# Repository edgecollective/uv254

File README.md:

# uv254

Open hardware for the **uv254** UV water-quality sensor. The device is three
boards, each its own KiCad project:

| Board | Folder | What's on it | Current design |
|---|---|---|---|
| **UV-Control** | [`hardware/uv-control`](hardware/uv-control) | nRF52840 controller (from Rook v0.4), ADS1115 ADC, color TFT, microSD, buttons | v0.4 (in progress: restarted from Rook v0.4) |
| **UV-Emitter** | [`hardware/uv-emitter`](hardware/uv-emitter) | Inolux IN-C35PPCTGU0 UV-C LED and its driver | v0.4 (released 2026-11-08) |
| **UV-Detector** | [`hardware/uv-detector`](hardware/uv-detector) | SD008-2171-112 photodiode with an op-amp front end | v0.5 (in progress: 3.3 V, 1.8 V reference, 7-pin connector); v0.4 released 2026-11-08 |

| [UV-Control](hardware/uv-control) | [UV-Emitter](hardware/uv-emitter) | [UV-Detector](hardware/uv-detector) |
|:---:|:---:|:---:|
|  |  |  |

Each board's README has its schematic, PCB layout and 3D views.

UV-Emitter was called *UV-LED-source* in earlier revisions. Background notes
are at <https://edgecollective.io/notes/uvf/>.

## Repository layout

```
hardware/
  uv-control/                 one KiCad project per board
    uv-control.kicad_pro      open this in KiCad
    uv-control.kicad_sch
    uv-control.kicad_pcb
    sym-lib-table             -> lib/uv254.kicad_sym
    fp-lib-table              -> lib/uv254.pretty
    docs/                     schematic PDF and the images in the board's README
    fab/<version>/            fabrication files that were actually sent out
  uv-emitter/
  uv-detector/
lib/                          shared project library (custom parts only)
  uv254.kicad_sym
  uv254.pretty/
firmware/uv-control/          CircuitPython scripts for the control board
scripts/build-fab.sh          builds gerbers, drill, BOM, PDF, positions
scripts/render-images.sh      renders schematic, layout and 3D images for the READMEs
.github/workflows/kicad.yml   ERC/DRC on every push; fab package on release tags
```

## Opening the boards

**[Download the latest design files (zip)](https://github.com/edgecollective/uv254/archive/refs/heads/main.zip)** if you just want to look
at or build the boards, or clone the repository to work on them. Either way,
open `hardware/<board>/<board>.kicad_pro` in **KiCad 10.0.x**, the version
everyone on the project uses (see [CONTRIBUTING.md](CONTRIBUTING.md)).

Keep the folder structure as it is. Custom parts come from `lib/` through each
project's own library tables, so you don't need any global library setup beyond
KiCad's standard libraries, but a board folder copied out on its own will be
missing its custom parts.

## Updating the board images

Each board's README shows its schematic, PCB layout and 3D views. These are
files in `hardware/<board>/docs/`, made by `scripts/render-images.sh`, so they
don't change by themselves when the design does. After changing a board, save
it in KiCad, then refresh the images from the top of the repository:

```sh
scripts/render-images.sh uv-detector                         # one board
scripts/render-images.sh uv-control uv-detector uv-emitter   # all three
```

Then commit what changed (`git status` shows it) along with the design change.

What the script does:

- Writes to `hardware/<board>/docs/`: the schematic as PDF and PNG, the PCB
  layout front and back (the back mirrored, as seen from below), and 3D renders
  front and back.
- Updates the image section of the board's README, between the
  `render-images` markers. Anything you write between those markers gets
  overwritten, so put your own notes outside them.
- Only replaces files whose picture changed. A board whose 3D look changed
  takes about 2 minutes (two raytraced renders). An unchanged board takes about
  15 seconds and leaves git clean.
- Uses KiCad's default colour theme, so everyone's images come out the same
  whatever their own KiCad preferences.

For a quick look while you work, `--fast` makes flat-shaded 3D renders in a few
seconds. Commit the full renders, though: run it again without `--fast` before
committing.

It needs KiCad 10 (`kicad-cli` on your `PATH`), plus Inkscape, ImageMagick and
poppler. On Debian or Ubuntu:

```sh
sudo apt install inkscape imagemagick poppler-utils
```

It has only been tested on Linux.

## Versions and releases

Each board is versioned on its own. A revision is a git tag named
`<board>/<version>`:

```
git tag -l 'uv-detector/*'          # list detector revisions
git checkout uv-detector/v0.3       # the exact design ordered from JLCPCB in Aug 2024
git checkout main                   # back to the current work
```

To download one revision as a zip, use its tag, for example
<https://github.com/edgecollective/uv254/archive/refs/tags/uv-detector/v0.3.zip>.

`hardware/<board>/fab/<version>/` holds the files that were actually sent to
the fab house for that revision. Each board's README has the revision history.
Pushing a new tag makes CI build that board's fab package and attach it to a
GitHub Release (see [CONTRIBUTING.md](CONTRIBUTING.md#releasing-a-board-revision)).

The history before this repository is in
[gitlab.com/edgecollective/uv-water](https://gitlab.com/edgecollective/uv-water).
Every tagged revision here was imported from it. The imported fab files were
checked by regenerating them from the tagged design.

## License

- **Hardware** (everything except `firmware/`): [CERN Open Hardware Licence
  Version 2 – Strongly Reciprocal](LICENSE) (CERN-OHL-S-2.0).
- **Firmware** (`firmware/`): [MIT License](firmware/uv-control/LICENSE). The
  bundled Adafruit libraries are also MIT, under Adafruit's copyright.

Contributors: Don Blair, Craig Versek.

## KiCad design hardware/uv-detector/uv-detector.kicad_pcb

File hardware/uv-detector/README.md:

# UV-Detector

Photodiode board: an SD008-2171-112 photodiode with an OPA4340 op-amp front
end. From v0.5 it runs from 3.3 V, with an MCP1501-18 1.8 V reference.

The cable connector is a 7-pin JST PH (J2), with a 0.1" header (J1) in
parallel:

| Pin | 1 | 2 | 3 | 4 | 5 | 6 | 7 |
|---|---|---|---|---|---|---|---|
| Signal | 3V3 | 1V8 (reference out) | light-tight (`LEAK`) | rect (`RECT`) | detect (`DTCT`) | GND | GND |

Open `uv-detector.kicad_pro` in KiCad 10. Custom parts come from
[`lib/`](../../lib).

**[Download the KiCad files (zip)](https://github.com/edgecollective/uv254/archive/refs/heads/main.zip)**: the whole repository as it is on
`main`, because the board needs the shared `lib/` folder. This board is in
`hardware/uv-detector/`.

<!-- render-images:start -->
<!-- Generated by scripts/render-images.sh. Edits between these markers are overwritten. -->

## Schematic

Click the image for the [PDF](docs/uv-detector-schematic.pdf).

## Board layout

Copper and silkscreen. The back is mirrored, as seen from below.

| Front | Back |
|:---:|:---:|
|  |  |

## 3D view

| Front | Back |
|:---:|:---:|
|  |  |

Images of the current design, made with `scripts/render-images.sh uv-detector`.
Re-run it after changing the board; see
[Updating the board images](../../README.md#updating-the-board-images).
<!-- render-images:end -->

## Revisions

| Version | Date | Status | Design | Fab files |
|---|---|---|---|---|
| v0.1 | 2024-03-12 | gerbers released | tag `uv-detector/v0.1` | [`fab/v0.1`](fab/v0.1) |
| v0.2 | 2024-04-06 | gerbers released | tag `uv-detector/v0.2` | [`fab/v0.2`](fab/v0.2) |
| v0.3 | 2024-08-19 | ordered from JLCPCB with emitter v0.3 and control v0.1 | tag `uv-detector/v0.3` | [`fab/v0.3`](fab/v0.3) |
| v0.2_A | 2026-06-26 | branched from v0.2; sent to Josh | tag `uv-detector/v0.2_A` | — |
| v0.2_B | 2026-10 | follows v0.2_A | tag `uv-detector/v0.2_B` | — |
| **v0.4** | 2026-11-08 | **gerbers released**; derived from v0.2_B | tag `uv-detector/v0.4` | [`fab/v0.4`](fab/v0.4) |
| v0.5 | — | in progress on `main` | `main` | — |

Notes:

- **v0.2**: the fabricated gerbers also include the copper text
  `uva-detect-v0.2` on F.Cu. It was deleted from the board before the design
  was committed. See [`fab/v0.2/README.md`](fab/v0.2/README.md).
- **v0.3** has no `.kicad_pro`, because it was never committed upstream. Open
  `uv-detector.kicad_pcb` or `.kicad_sch` directly at that tag.
- **v0.4** was called "v0.3" in `uv-water`. It was renumbered because v0.3 was
  already used by the 2024 JLCPCB order.
- **v0.5** (in progress) moves to the system-wide 3.3 V supply: the op-amp runs
  from 3.3 V instead of 5 V, and an MCP1501-18 (1.8 V, buffered) replaces the
  LM4040 2.5 V shunt reference and its feed resistor. The connectors grow from
  6 to 7 pins, the extra pin being a second GND. Signal swing above the
  reference drops from 2.5 V to 1.5 V, so the gain values may need adjusting.

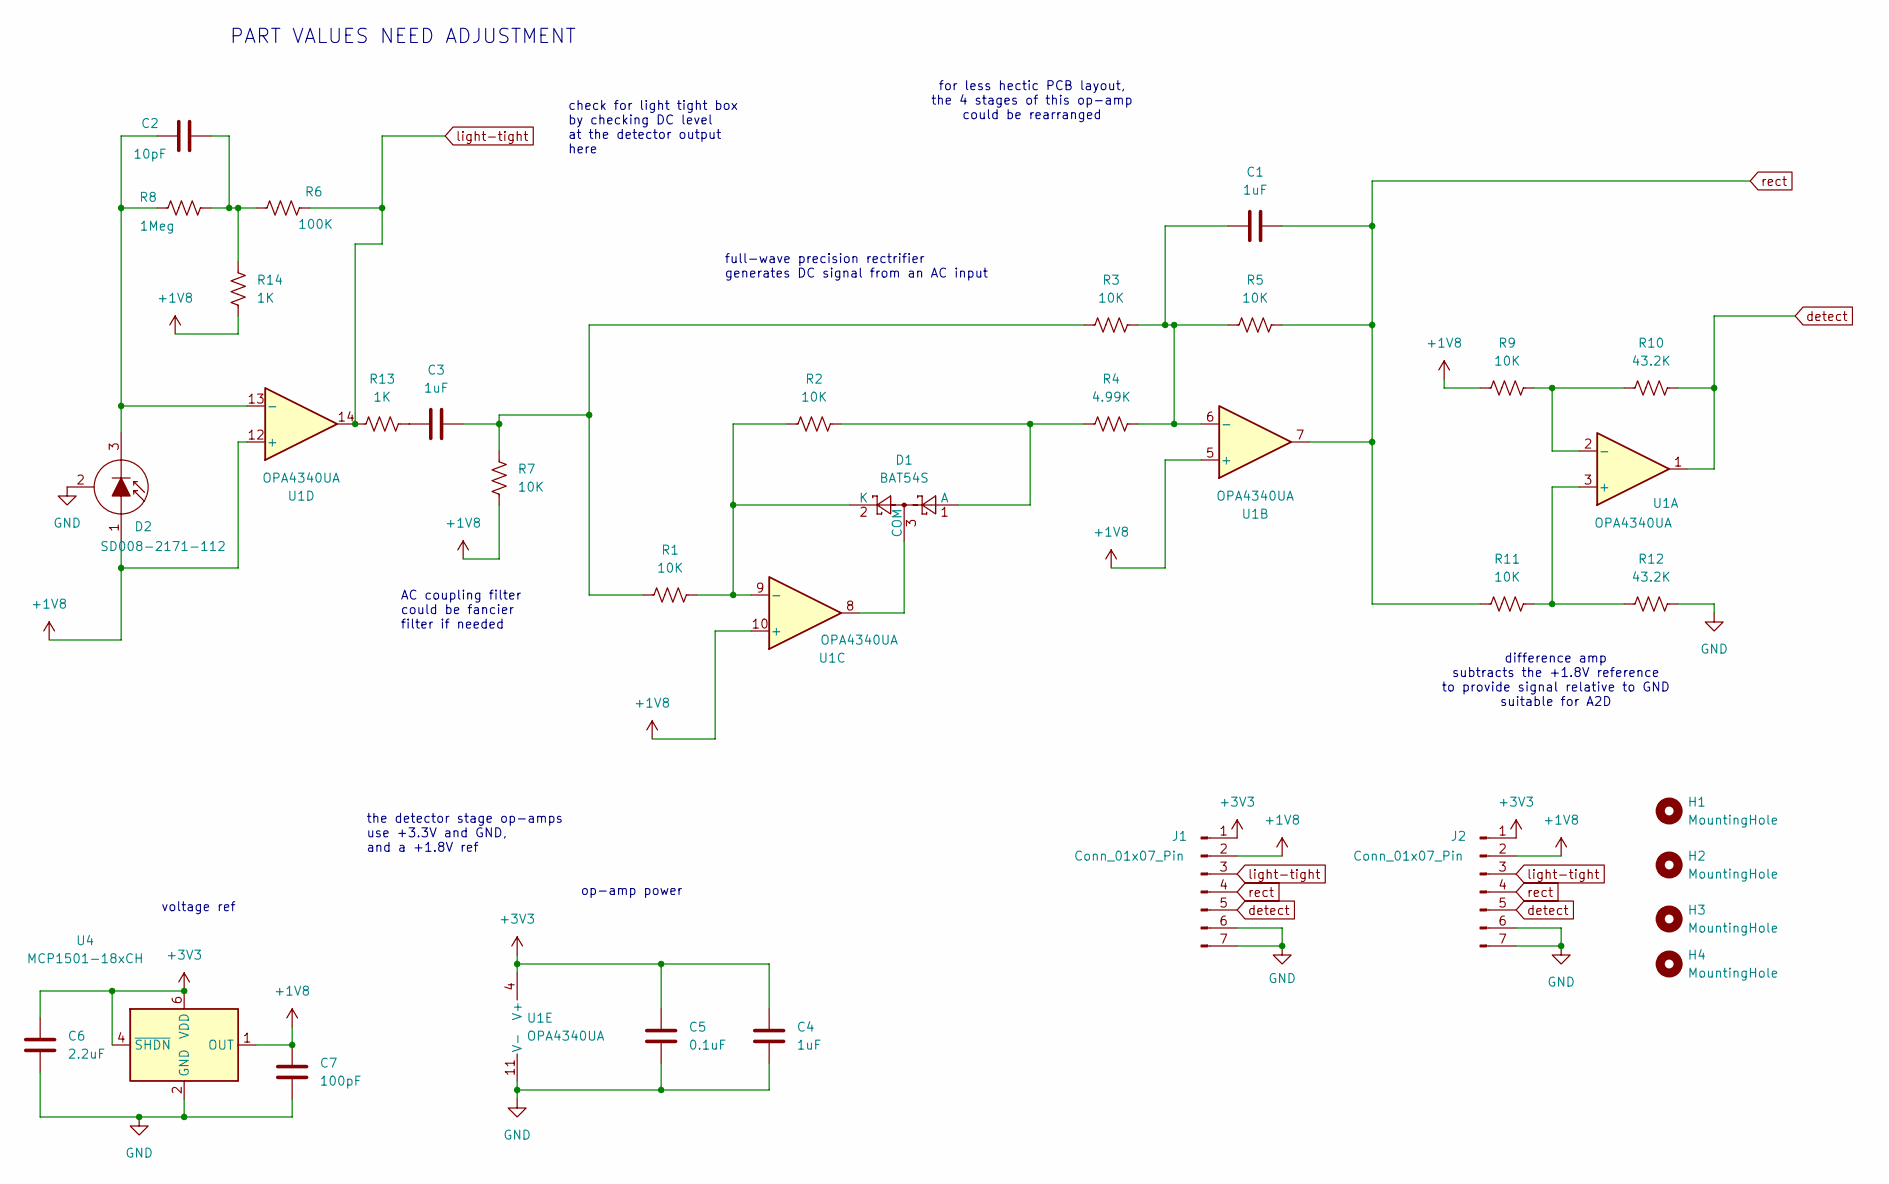
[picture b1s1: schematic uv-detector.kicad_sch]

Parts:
C1, C3, C4: 1uF; C_0805_2012Metric_Pad1.18x1.45mm_HandSolder
C2: 10pF; C_0805_2012Metric_Pad1.18x1.45mm_HandSolder
C5: 0.1uF; C_0805_2012Metric_Pad1.18x1.45mm_HandSolder
C6: 2.2uF; C_0805_2012Metric_Pad1.18x1.45mm_HandSolder
C7: 100pF; C_0805_2012Metric_Pad1.18x1.45mm_HandSolder
D1: BAT54S; SOT-23
D2: SD008-2171-112; TO-18-3
H1, H2, H3, H4: MountingHole; MountingHole_3.2mm_M3
J1: Conn_01x07_Pin; PinHeader_1x07_P2.54mm_Vertical
J2: Conn_01x07_Pin; JST_PH_B7B-PH-K_1x07_P2.00mm_Vertical
R1, R2, R3, R5, R7, R9, R11: 10K; R_0805_2012Metric_Pad1.20x1.40mm_HandSolder
R4: 4.99K; R_0805_2012Metric_Pad1.20x1.40mm_HandSolder
R6: 100K; R_0805_2012Metric_Pad1.20x1.40mm_HandSolder
R8: 1Meg; R_0805_2012Metric_Pad1.20x1.40mm_HandSolder
R10, R12: 43.2K; R_0805_2012Metric_Pad1.20x1.40mm_HandSolder
R13, R14: 1K; R_0805_2012Metric_Pad1.20x1.40mm_HandSolder
U1: OPA4340UA; SOIC-14_3.9x8.7mm_P1.27mm
U4: MCP1501-18xCH; SOT-23-6

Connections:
+1V8: C7.2, D2.1, J1.2, J2.2, R7.1, R9.1, R14.1, U1.5 (+), U1.10 (+), U1.12 (+), U4.1 (OUT)
+3V3: C4.2, C5.2, C6.2, J1.1, J2.1, U1.4 (V+), U4.4 (~SHDN), U4.6 (VDD)
GND: C4.1, C5.1, C6.1, C7.1, D2.2 (C), J1.6, J1.7, J2.6, J2.7, R12.2, U1.11 (V-), U4.2 (GND), U4.3 (GND), U4.5 (GND)
unnamed: C2.2, R6.1, R8.2, R14.2
unnamed: C3.1, R13.1
unnamed: C3.2, R1.1, R3.1, R7.2
unnamed: D1.1 (A), R2.2, R4.1
unnamed: D1.3 (COM), U1.8
unnamed: D1.2 (K), R1.2, R2.1, U1.9 (-)
unnamed: C2.1, D2.3 (K), R8.1, U1.13 (-)
unnamed: R11.2, R12.1, U1.3 (+)
unnamed: R9.2, R10.1, U1.2 (-)
unnamed: C1.1, R3.2, R4.2, R5.1, U1.6 (-)
detect: J1.5, J2.5, R10.2, U1.1
light-tight: J1.3, J2.3, R6.2, R13.2, U1.14
rect: C1.2, J1.4, J2.4, R5.2, R11.1, U1.7

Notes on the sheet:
PART VALUES NEED ADJUSTMENT
op-amp power
for less hectic PCB layout, the 4 stages of this op-amp could be rearranged
full-wave precision rectrifier generates DC signal from an AC input
AC coupling filter could be fancier filter if needed
voltage ref
check for light tight box by checking DC level at the detector output here
the detector stage op-amps use +3.3V and GND, and a +1.8V ref
difference amp subtracts the +1.8V reference to provide signal relative to GND suitable for A2D

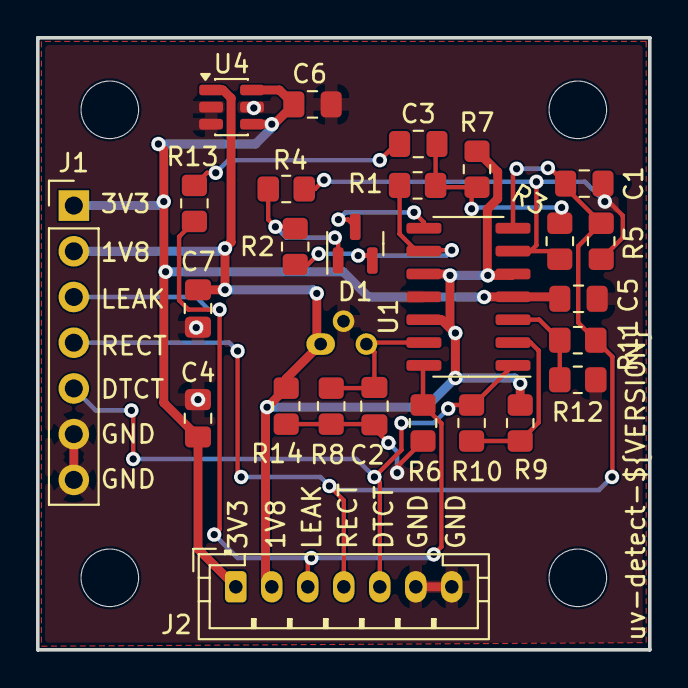
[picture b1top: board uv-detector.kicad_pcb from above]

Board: 2 copper layers, 34.0 x 34.0 mm, 31 parts (1 on the bottom side), 16 nets.

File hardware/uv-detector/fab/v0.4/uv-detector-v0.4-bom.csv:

"Refs","Value","Footprint","Qty","DNP","Description"
"C1,C3,CX4,CX5","1uF","Capacitor_SMD:C_0805_2012Metric_Pad1.18x1.45mm_HandSolder","4","",""
"C2","10pF","Capacitor_SMD:C_0805_2012Metric_Pad1.18x1.45mm_HandSolder","1","",""
"C4,C5","0.1uF","Capacitor_SMD:C_0805_2012Metric_Pad1.18x1.45mm_HandSolder","2","",""
"D1","BAT54S","Package_TO_SOT_SMD:SOT-23","1","",""
"D2","SD008-2171-112","Package_TO_SOT_THT:TO-18-3","1","","Si PIN Photodiode, 0.1 GHz, TO-18-3"
"H1,H2,H3,H4","MountingHole","MountingHole:MountingHole_3.2mm_M3","4","","Mounting Hole without connection"
"J1","Conn_01x06_Male","Connector_PinHeader_2.54mm:PinHeader_1x06_P2.54mm_Vertical","1","","Generic connector, single row, 01x06, script generated (kicad-library-utils/schlib/autogen/connector/)"
"J2","Conn_01x06_Male","Connector_JST:JST_PH_B6B-PH-K_1x06_P2.00mm_Vertical","1","","Generic connector, single row, 01x06, script generated (kicad-library-utils/schlib/autogen/connector/)"
"R1,R2,R3,R5,R7,R9,R11","10K","Resistor_SMD:R_0805_2012Metric_Pad1.20x1.40mm_HandSolder","7","",""
"R4,R15","4.99K","Resistor_SMD:R_0805_2012Metric_Pad1.20x1.40mm_HandSolder","2","",""
"R8","1Meg","Resistor_SMD:R_0805_2012Metric_Pad1.20x1.40mm_HandSolder","1","",""
"R14,RX13","1K","Resistor_SMD:R_0805_2012Metric_Pad1.20x1.40mm_HandSolder","2","",""
"RX6","100K","Resistor_SMD:R_0805_2012Metric_Pad1.20x1.40mm_HandSolder","1","",""
"RX10,RX12","43.2K","Resistor_SMD:R_0805_2012Metric_Pad1.20x1.40mm_HandSolder","2","",""
"U1","OPA4340UA","Package_SO:SOIC-14_3.9x8.7mm_P1.27mm","1","",""
"U2","LM4040DBZ-2.5","Package_TO_SOT_SMD:SOT-23","1","","2.500V Precision Micropower Shunt Voltage Reference, SOT-23"

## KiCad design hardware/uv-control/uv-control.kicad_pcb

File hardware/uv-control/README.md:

# UV-Control

Controller board. **v0.4 is in progress on `main`, restarted from Rook v0.4**
(Edge Collective's validated Pro Micro nRF52840 board): its Pro Micro, ST7789
display, buttons and microSD, plus an ADS1115 ADC, JST connectors to the emitter
and detector, and test points. The boost for the UV LED is still to be added. See
[`v0.4-design.md`](v0.4-design.md) for the pin map and what's left to do. The
first v0.4 draft is in [`reference/v0.4-draft`](reference/v0.4-draft).

v0.1 (fabricated in 2024) used an Adafruit ItsyBitsy nRF52840 Express, an
SSD1306 OLED display, push buttons and a 555-based boost circuit.

Firmware is in [`firmware/uv-control`](../../firmware/uv-control). The v0.4
bring-up code is in its [`v0.4`](../../firmware/uv-control/v0.4) folder.

Open `uv-control.kicad_pro` in KiCad 10. Custom parts come from
[`lib/`](../../lib).

**[Download the KiCad files (zip)](https://github.com/edgecollective/uv254/archive/refs/heads/main.zip)**: the whole repository as it is on
`main`, because the board needs the shared `lib/` folder. This board is in
`hardware/uv-control/`.

<!-- render-images:start -->
<!-- Generated by scripts/render-images.sh. Edits between these markers are overwritten. -->

## Schematic

Click the image for the [PDF](docs/uv-control-schematic.pdf).

## Board layout

Copper and silkscreen. The back is mirrored, as seen from below.

| Front | Back |
|:---:|:---:|
|  |  |

## 3D view

| Front | Back |
|:---:|:---:|
|  |  |

Images of the current design, made with `scripts/render-images.sh uv-control`.
Re-run it after changing the board; see
[Updating the board images](../../README.md#updating-the-board-images).
<!-- render-images:end -->

## Revisions

| Version | Date | Status | Design | Fab files |
|---|---|---|---|---|
| v0.1 | 2024-07-29 | gerbers released; ordered from JLCPCB on 2024-08-19 | tag `uv-control/v0.1` | [`fab/v0.1`](fab/v0.1) |
| v0.1_A | 2026-06-26 | branched from v0.1; sent to Josh | tag `uv-control/v0.1_A` | — |
| v0.1_A+ | 2026-10 | edits made after v0.1_A was sent; never fabricated; superseded by v0.4 | commit `db4232b` | — |
| **v0.4** | 2026-11 | **in progress on `main`**: first-draft schematic; layout not started | `main` | — |

Notes:

- **v0.1_A+** isn't tagged. To get it back: `git checkout db4232b -- hardware/uv-control`.
  Its silkscreen points to `gitlab.com/edgecollective/uv-water/` and reads
  `UV-Control v0.1 / July 2024`.

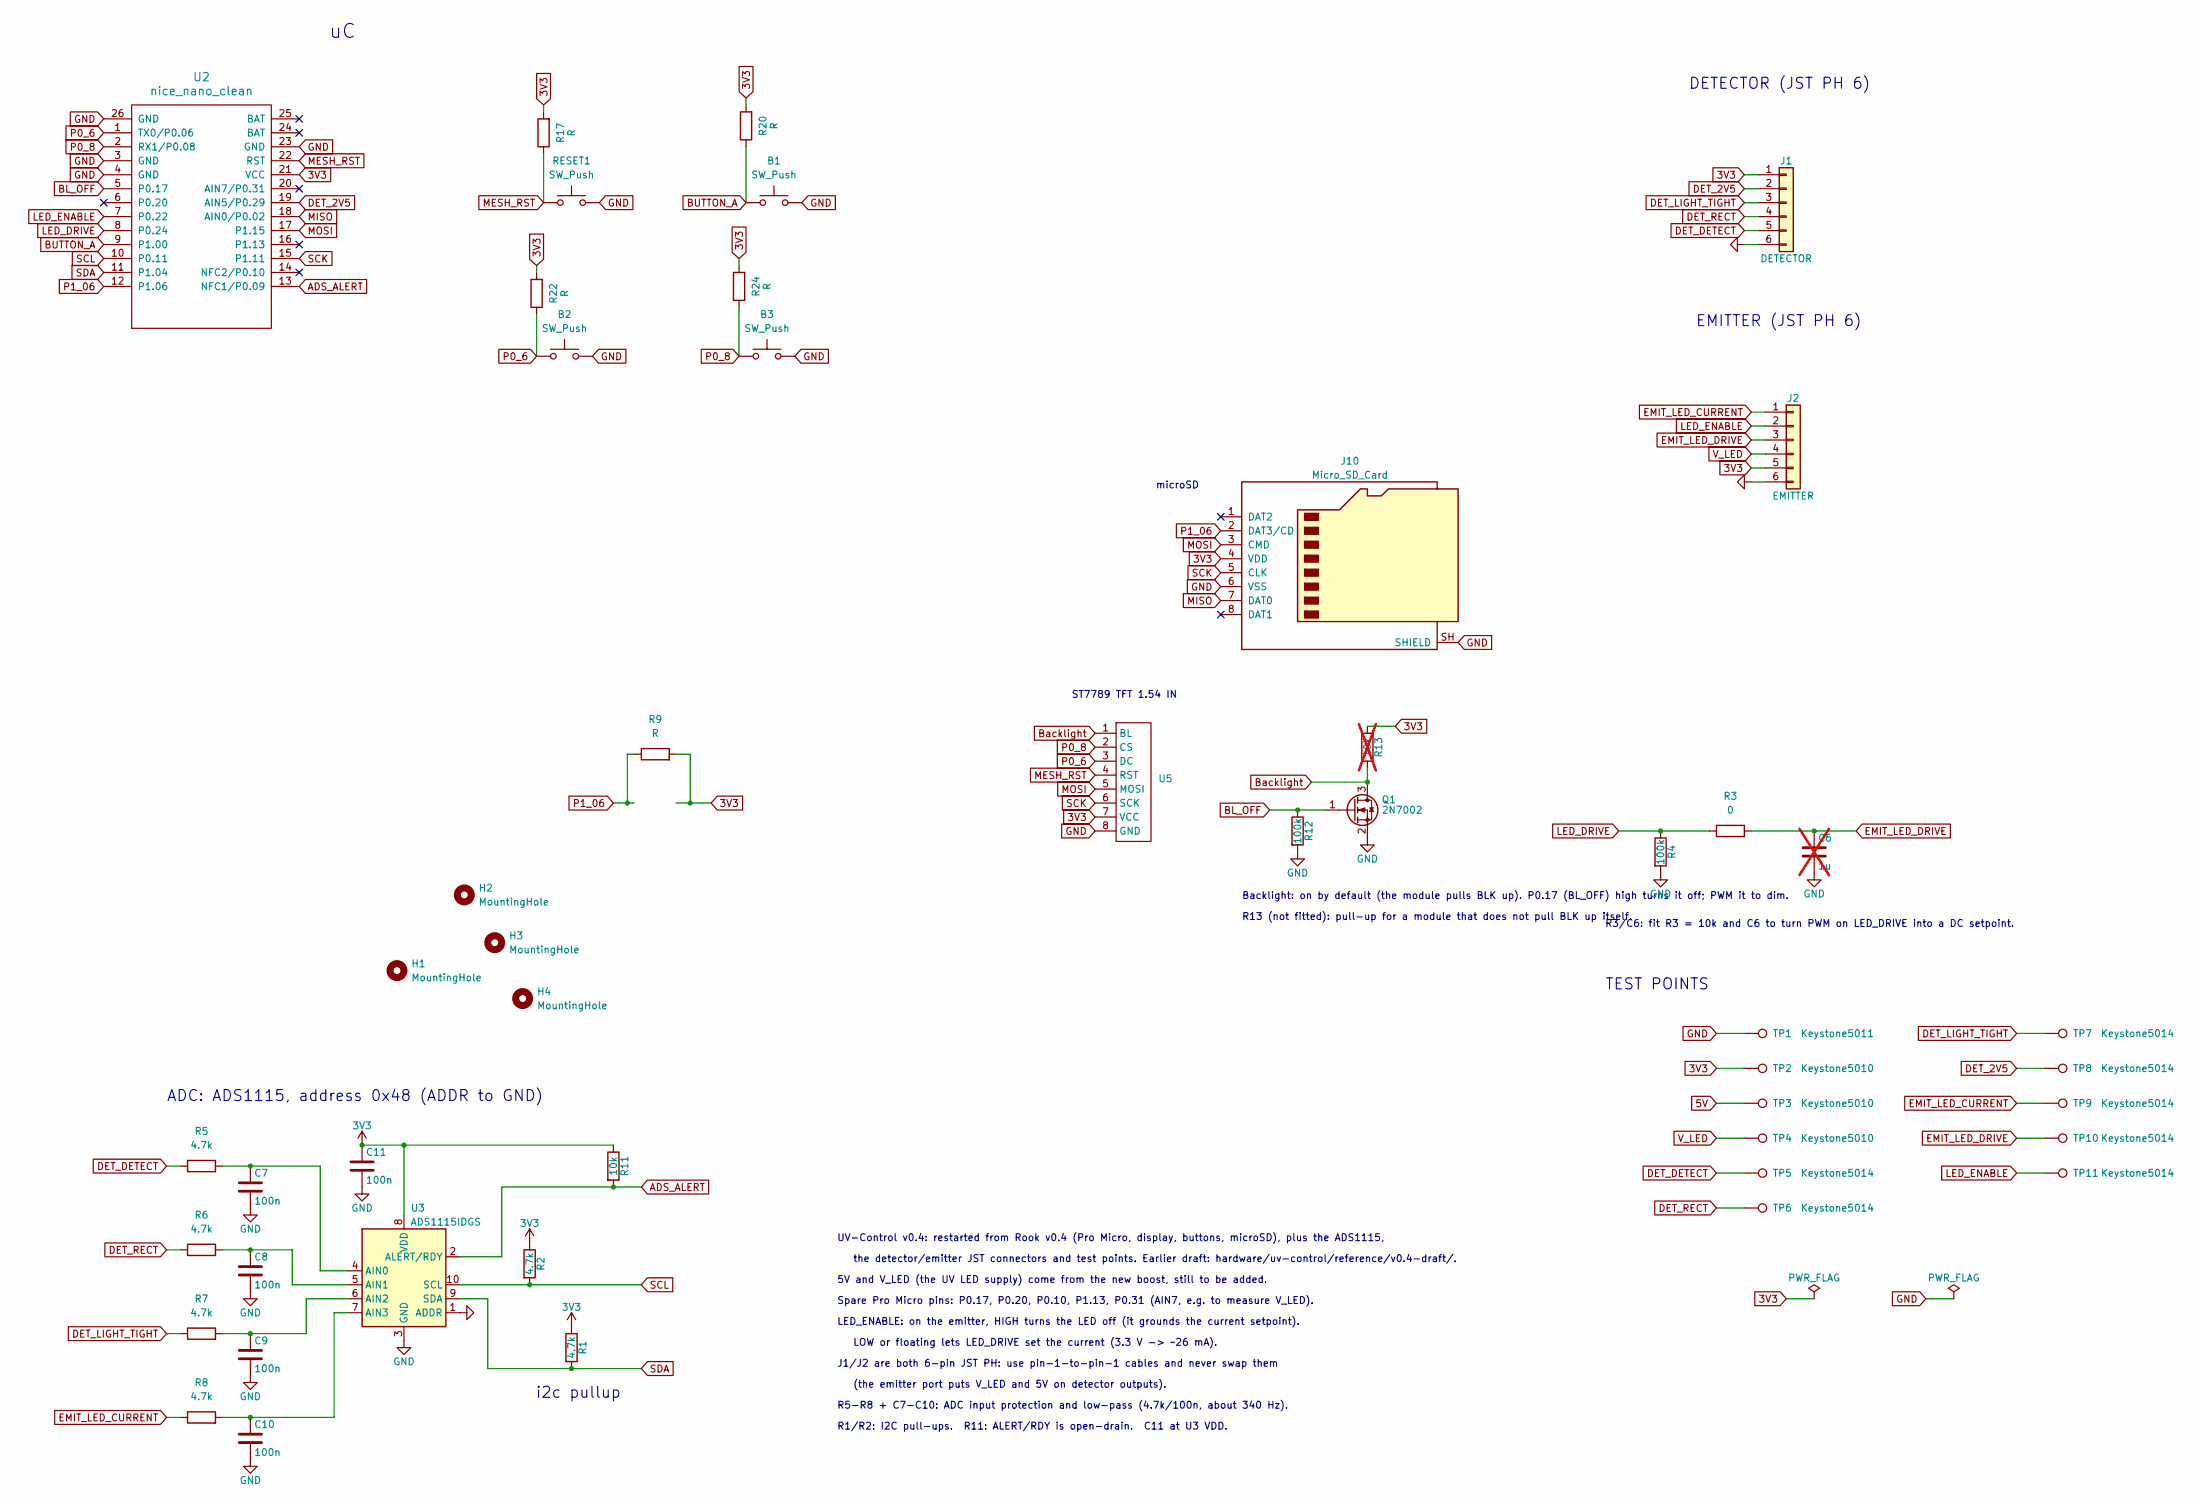
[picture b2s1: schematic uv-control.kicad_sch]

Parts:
B1, B2, B3: SW_Push; SW_Tactile_12x12_B3F-40xx
C6: 1u; C_0805_2012Metric; not fitted
C7, C8, C9, C10, C11: 100n; C_0805_2012Metric
H1, H2, H3, H4: MountingHole; MountingHole_3.2mm_M3
J1: DETECTOR; JST_PH_B6B-PH-K_1x06_P2.00mm_Vertical
J2: EMITTER; JST_PH_B6B-PH-K_1x06_P2.00mm_Vertical
J10: Micro_SD_Card; DM3D-SF_outline
Q1: 2N7002; SOT-23
R1, R2, R5, R6, R7, R8: 4.7k; R_0805_2012Metric
R3: 0; R_0805_2012Metric
R4, R12: 100k; R_0805_2012Metric
R9, R17, R20, R22, R24: R; R_0805_2012Metric_Pad1.20x1.40mm_HandSolder
R11: 10k; R_0805_2012Metric
R13: 10k; R_0805_2012Metric; not fitted
RESET1: SW_Push; SW_PUSH_6mm_H5mm
TP1: Keystone5011; TestPoint_Keystone_5010-5014_Multipurpose
TP2, TP3, TP4: Keystone5010; TestPoint_Keystone_5010-5014_Multipurpose
TP5, TP6, TP7, TP8, TP9, TP10, TP11: Keystone5014; TestPoint_Keystone_5010-5014_Multipurpose
U2: nice_nano_clean; nice_nano_cleanest
U3: ADS1115IDGS; TSSOP-10_3x3mm_P0.5mm
U5: st7789_154in_240x240

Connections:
3V3: C11.1, J1.1, J2.5, J10.4 (VDD), R1.1, R2.1, R9.2, R11.1, R13.1, R17.2, R20.2, R22.2, R24.2, TP2.1 (1_1), U2.21 (VCC), U3.8 (VDD), U5.7 (VCC)
5V: TP3.1 (1_1)
ADS_ALERT: R11.2, U2.13 (NFC1/P0.09), U3.2 (ALERT/RDY)
BL_OFF: Q1.1 (G), R12.1, U2.5 (P0.17)
BUTTON_A: B1.1, R20.1, U2.9 (P1.00)
Backlight: Q1.3 (D), R13.2, U5.1 (BL)
DET_2V5: J1.2, TP8.1 (1_1), U2.19 (AIN5/P0.29)
DET_DETECT: J1.5, R5.1, TP5.1 (1_1)
DET_LIGHT_TIGHT: J1.3, R7.1, TP7.1 (1_1)
DET_RECT: J1.4, R6.1, TP6.1 (1_1)
EMIT_LED_CURRENT: J2.1, R8.1, TP9.1 (1_1)
EMIT_LED_DRIVE: C6.1, J2.3, R3.2, TP10.1 (1_1)
GND: B1.2, B2.2, B3.2, C6.2, C7.2, C8.2, C9.2, C10.2, C11.2, J1.6, J2.6, J10.6 (VSS), J10.SH (SHIELD), Q1.2 (S), R4.2, R12.2, RESET1.2, TP1.1 (1_1), U2.3 (GND), U2.4 (GND), U2.23 (GND), U2.26 (GND), U3.1 (ADDR), U3.3 (GND), U5.8 (GND)
LED_DRIVE: R3.1, R4.1, U2.8 (P0.24)
LED_ENABLE: J2.2, TP11.1 (1_1), U2.7 (P0.22)
MESH_RST: R17.1, RESET1.1, U2.22 (RST), U5.4 (RST)
MISO: J10.7 (DAT0), U2.18 (AIN0/P0.02)
MOSI: J10.3 (CMD), U2.17 (P1.15), U5.5 (MOSI)
unnamed: C7.1, R5.2, U3.4 (AIN0)
unnamed: C8.1, R6.2, U3.5 (AIN1)
unnamed: C9.1, R7.2, U3.6 (AIN2)
unnamed: C10.1, R8.2, U3.7 (AIN3)
P0_6: B2.1, R22.1, U2.1 (TX0/P0.06), U5.3 (DC)
P0_8: B3.1, R24.1, U2.2 (RX1/P0.08), U5.2 (CS)
P1_06: J10.2 (DAT3/CD), R9.1, U2.12 (P1.06)
SCK: J10.5 (CLK), U2.15 (P1.11), U5.6 (SCK)
SCL: R2.2, U2.10 (P0.11), U3.10 (SCL)
SDA: R1.2, U2.11 (P1.04), U3.9 (SDA)
V_LED: J2.4, TP4.1 (1_1)

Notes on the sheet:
microSD
EMITTER (JST PH 6)
TEST POINTS
5V and V_LED (the UV LED supply) come from the new boost, still to be added.
ADC: ADS1115, address 0x48 (ADDR to GND)
R5-R8 + C7-C10: ADC input protection and low-pass (4.7k/100n, about 340 Hz).
ST7789 TFT 1.54 IN
J1/J2 are both 6-pin JST PH: use pin-1-to-pin-1 cables and never swap them
i2c pullup
Spare Pro Micro pins: P0.17, P0.20, P0.10, P1.13, P0.31 (AIN7, e.g. to measure V_LED).
DETECTOR (JST PH 6)
UV-Control v0.4: restarted from Rook v0.4 (Pro Micro, display, buttons, microSD), plus the ADS1115,
R3/C6: fit R3 = 10k and C6 to turn PWM on LED_DRIVE into a DC setpoint.
Backlight: on by default (the module pulls BLK up). P0.17 (BL_OFF) high turns it off; PWM it to dim.
R1/R2: I2C pull-ups. R11: ALERT/RDY is open-drain. C11 at U3 VDD.
the detector/emitter JST connectors and test points. Earlier draft: hardware/uv-control/reference/v0.4-draft/.
R13 (not fitted): pull-up for a module that does not pull BLK up itself.
LED_ENABLE: on the emitter, HIGH turns the LED off (it grounds the current setpoint).
LOW or floating lets LED_DRIVE set the current (3.3 V -> ~26 mA).
(the emitter port puts V_LED and 5V on detector outputs).

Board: 2 copper layers, 48 parts (39 on the bottom side), 28 nets, no tracks yet.

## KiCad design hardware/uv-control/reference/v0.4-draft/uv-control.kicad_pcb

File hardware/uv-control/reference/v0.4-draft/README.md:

# UV-Control v0.4: first draft (reference only)

The first v0.4 control-board draft, kept for reference when the board was
restarted from Rook v0.4 on 2026-11-13. It is the state of `main` at commit
`87ac380` plus the edits made on 2026-11-13 before the restart (schematic tidy-up
and a start on the PCB).

- `uv-control.kicad_sch`, `.kicad_pcb`, `.kicad_pro`: the KiCad project. Opens
  on its own; library tables point at the shared `lib/`. Its Pro Micro symbol
  (`ProMicro_nRF52840`) is embedded in the schematic; the matching footprint is
  only in the PCB and in git history.
- `uv-control-v0.4-draft-schematic.pdf`: the schematic.
- `v0.4-design.md`: the design notes for this draft (pin map, LMR62014 8 V boost,
  checks before building).

The ADS1115 block, the detector/emitter JST connectors and the LED_DRIVE parts
were carried over into the restarted board. The LMR62014 boost was not.

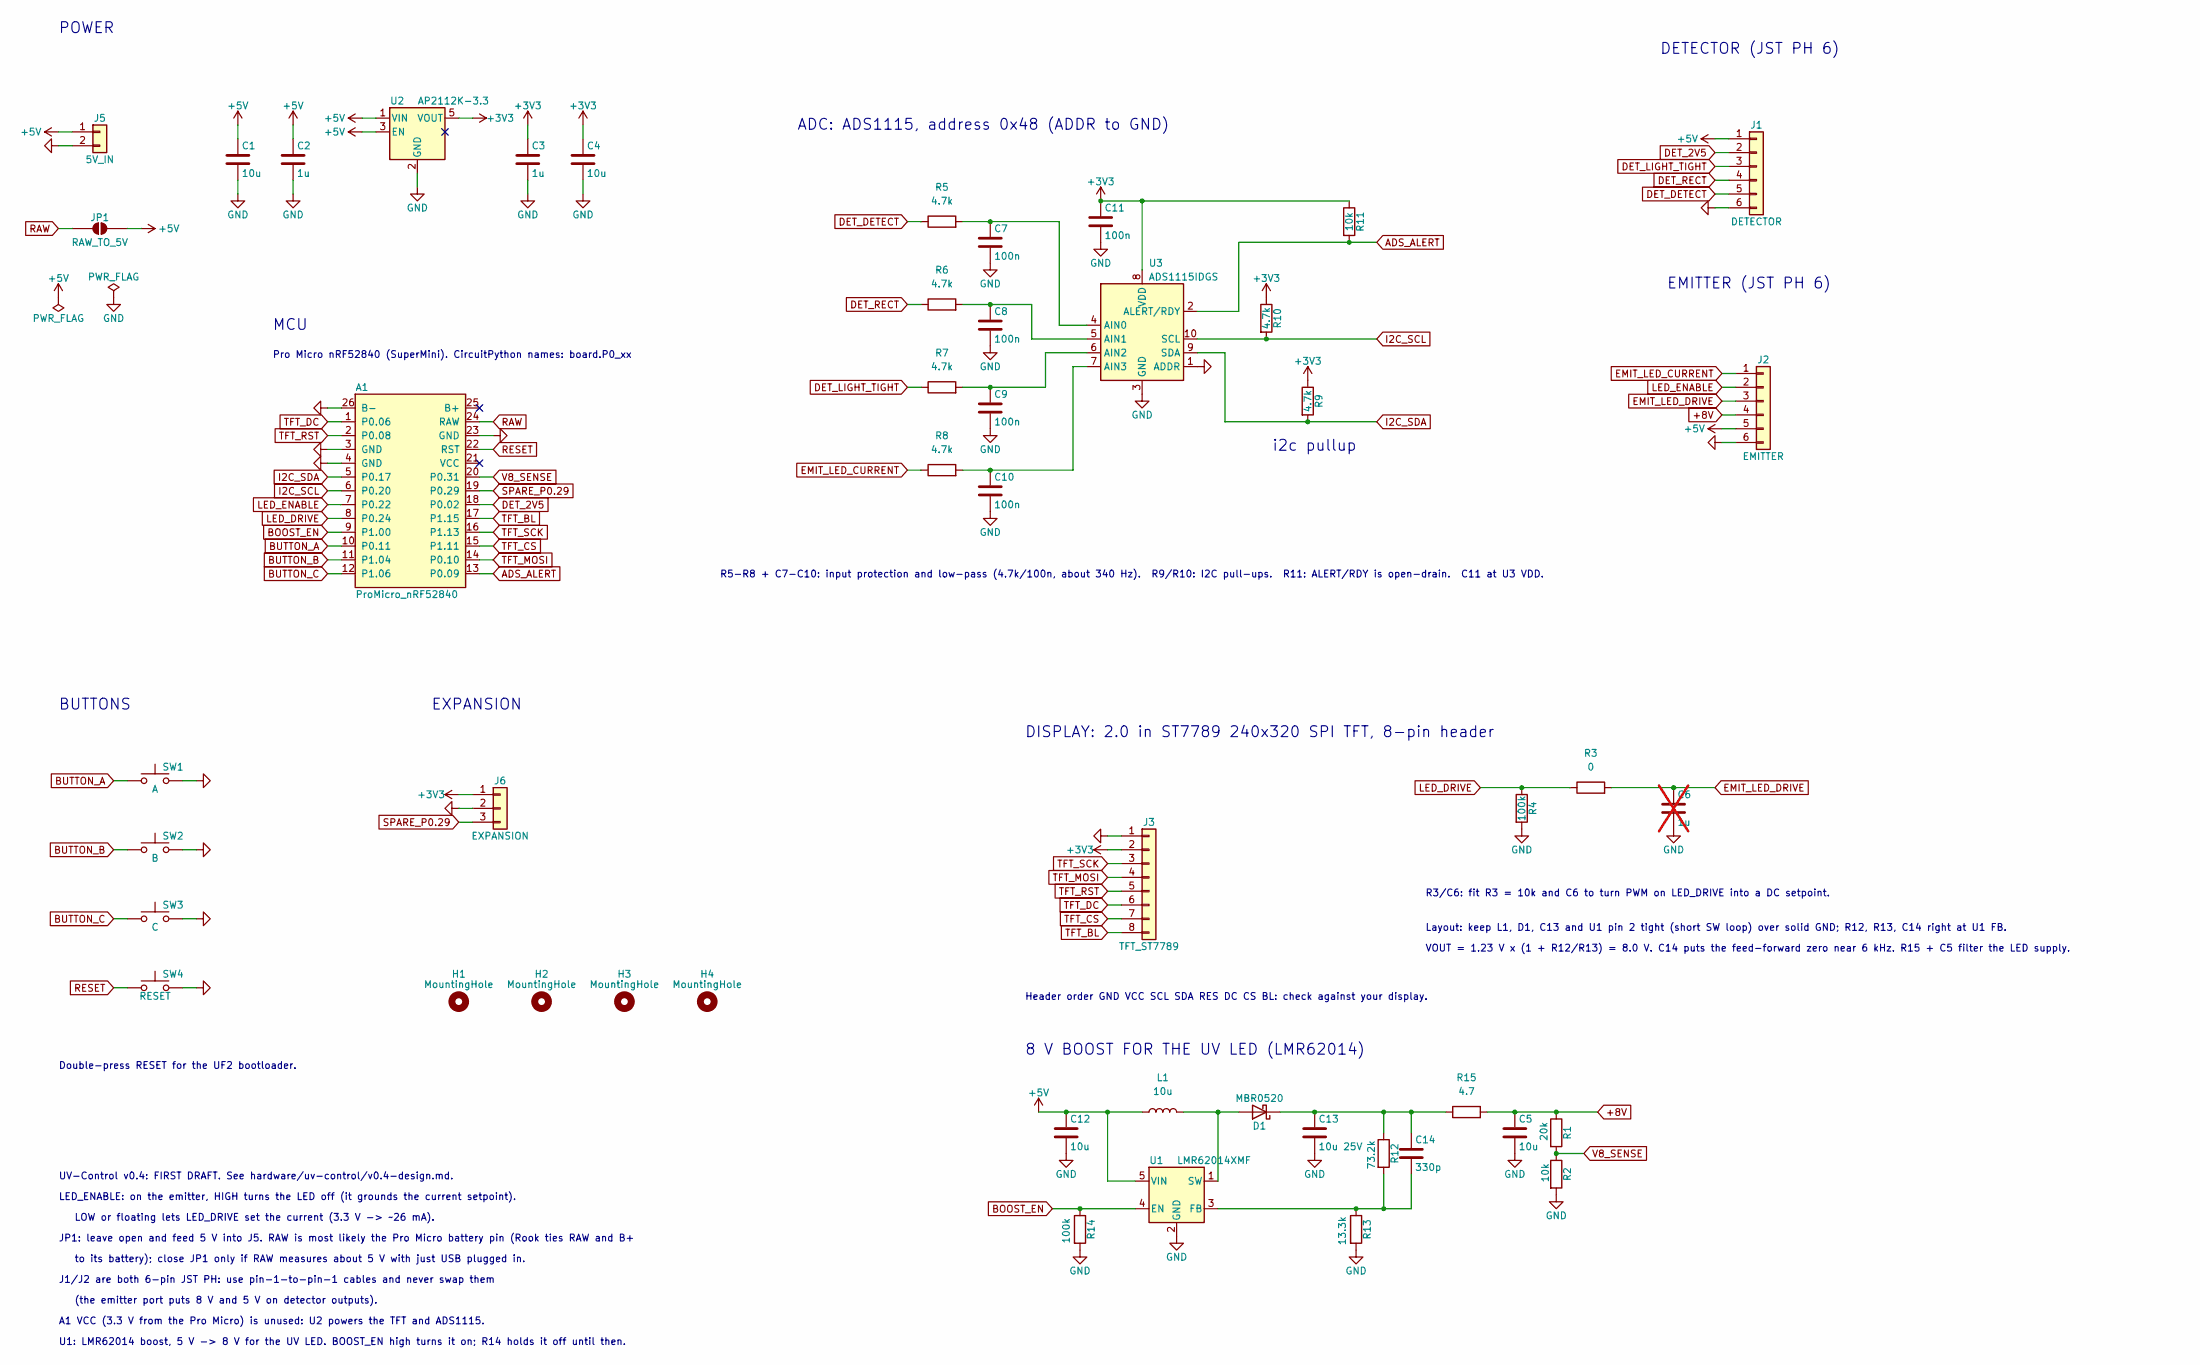
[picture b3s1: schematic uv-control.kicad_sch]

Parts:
A1: ProMicro_nRF52840
C1, C4, C5, C12: 10u; C_0805_2012Metric
C2, C3: 1u; C_0805_2012Metric
C6: 1u; C_0805_2012Metric; not fitted
C7, C8, C9, C10, C11: 100n; C_0805_2012Metric
C13: 10u 25V; C_1206_3216Metric
C14: 330p; C_0805_2012Metric
D1: MBR0520; D_SOD-123
H1, H2, H3, H4: MountingHole; MountingHole_3.2mm_M3
J1: DETECTOR; JST_PH_B6B-PH-K_1x06_P2.00mm_Vertical
J2: EMITTER; JST_PH_B6B-PH-K_1x06_P2.00mm_Vertical
J3: TFT_ST7789; PinHeader_1x08_P2.54mm_Vertical
J5: 5V_IN; JST_PH_B2B-PH-K_1x02_P2.00mm_Vertical
J6: EXPANSION; PinHeader_1x03_P2.54mm_Vertical
JP1: RAW_TO_5V; SolderJumper-2_P1.3mm_Open_Pad1.0x1.5mm
L1: 10u; L_Bourns-SRN4018
R1: 20k; R_0805_2012Metric
R2, R11: 10k; R_0805_2012Metric
R3: 0; R_0805_2012Metric
R4, R14: 100k; R_0805_2012Metric
R5, R6, R7, R8, R9, R10: 4.7k; R_0805_2012Metric
R12: 73.2k; R_0805_2012Metric
R13: 13.3k; R_0805_2012Metric
R15: 4.7; R_0805_2012Metric
SW1: A; SW_Tactile_SPST_Angled_PTS645Vx31-2LFS
SW2: B; SW_Tactile_SPST_Angled_PTS645Vx31-2LFS
SW3: C; SW_Tactile_SPST_Angled_PTS645Vx31-2LFS
SW4: RESET; SW_Tactile_SPST_Angled_PTS645Vx31-2LFS
U1: LMR62014XMF; SOT-23-5
U2: AP2112K-3.3; SOT-23-5
U3: ADS1115IDGS; TSSOP-10_3x3mm_P0.5mm

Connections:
+3V3: C3.1, C4.1, C11.1, J3.2, J6.1, R9.1, R10.1, R11.1, U2.5 (VOUT), U3.8 (VDD)
+5V: C1.1, C2.1, C12.1, J1.1, J2.5, J5.1, JP1.2 (B), L1.1, U1.5 (VIN), U2.1 (VIN), U2.3 (EN)
+8V: C5.1, J2.4, R1.1, R15.2
ADS_ALERT: A1.13 (P0.09), R11.2, U3.2 (ALERT/RDY)
BOOST_EN: A1.9 (P1.00), R14.1, U1.4 (EN)
BUTTON_A: A1.10 (P0.11), SW1.1
BUTTON_B: A1.11 (P1.04), SW2.1
BUTTON_C: A1.12 (P1.06), SW3.1
DET_2V5: A1.18 (P0.02), J1.2
DET_DETECT: J1.5, R5.1
DET_LIGHT_TIGHT: J1.3, R7.1
DET_RECT: J1.4, R6.1
EMIT_LED_CURRENT: J2.1, R8.1
EMIT_LED_DRIVE: C6.1, J2.3, R3.2
GND: A1.3 (GND), A1.4 (GND), A1.23 (GND), A1.26 (B-), C1.2, C2.2, C3.2, C4.2, C5.2, C6.2, C7.2, C8.2, C9.2, C10.2, C11.2, C12.2, C13.2, J1.6, J2.6, J3.1, J5.2, J6.2, R2.2, R4.2, R13.2, R14.2, SW1.2, SW2.2, SW3.2, SW4.2, U1.2 (GND), U2.2 (GND), U3.1 (ADDR), U3.3 (GND)
I2C_SCL: A1.6 (P0.20), R10.2, U3.10 (SCL)
I2C_SDA: A1.5 (P0.17), R9.2, U3.9 (SDA)
LED_DRIVE: A1.8 (P0.24), R3.1, R4.1
LED_ENABLE: A1.7 (P0.22), J2.2
unnamed: D1.2 (A), L1.2, U1.1 (SW)
unnamed: C13.1, C14.1, D1.1 (K), R12.1, R15.1
unnamed: C14.2, R12.2, R13.1, U1.3 (FB)
unnamed: C7.1, R5.2, U3.4 (AIN0)
unnamed: C8.1, R6.2, U3.5 (AIN1)
unnamed: C9.1, R7.2, U3.6 (AIN2)
unnamed: C10.1, R8.2, U3.7 (AIN3)
RAW: A1.24 (RAW), JP1.1 (A)
RESET: A1.22 (RST), SW4.1
SPARE_P0.29: A1.19 (P0.29), J6.3
TFT_BL: A1.17 (P1.15), J3.8
TFT_CS: A1.15 (P1.11), J3.7
TFT_DC: A1.1 (P0.06), J3.6
TFT_MOSI: A1.14 (P0.10), J3.4
TFT_RST: A1.2 (P0.08), J3.5
TFT_SCK: A1.16 (P1.13), J3.3
V8_SENSE: A1.20 (P0.31), R1.2, R2.1

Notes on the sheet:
UV-Control v0.4: FIRST DRAFT. See hardware/uv-control/v0.4-design.md.
VOUT = 1.23 V x (1 + R12/R13) = 8.0 V. C14 puts the feed-forward zero near 6 kHz. R15 + C5 filter the LED supply.
Double-press RESET for the UF2 bootloader.
POWER
Header order GND VCC SCL SDA RES DC CS BL: check against your display.
to its battery); close JP1 only if RAW measures about 5 V with just USB plugged in.
EMITTER (JST PH 6)
(the emitter port puts 8 V and 5 V on detector outputs).
ADC: ADS1115, address 0x48 (ADDR to GND)
BUTTONS
Pro Micro nRF52840 (SuperMini). CircuitPython names: board.P0_xx
R5-R8 + C7-C10: input protection and low-pass (4.7k/100n, about 340 Hz). R9/R10: I2C pull-ups. R11: ALERT/RDY is open-drain. C11 at U3 VDD.
A1 VCC (3.3 V from the Pro Micro) is unused: U2 powers the TFT and ADS1115.
i2c pullup
DETECTOR (JST PH 6)
R3/C6: fit R3 = 10k and C6 to turn PWM on LED_DRIVE into a DC setpoint.
LOW or floating lets LED_DRIVE set the current (3.3 V -> ~26 mA).
Layout: keep L1, D1, C13 and U1 pin 2 tight (short SW loop) over solid GND; R12, R13, C14 right at U1 FB.
JP1: leave open and feed 5 V into J5. RAW is most likely the Pro Micro battery pin (Rook ties RAW and B+
EXPANSION
LED_ENABLE: on the emitter, HIGH turns the LED off (it grounds the current setpoint).
J1/J2 are both 6-pin JST PH: use pin-1-to-pin-1 cables and never swap them
MCU
U1: LMR62014 boost, 5 V -> 8 V for the UV LED. BOOST_EN high turns it on; R14 holds it off until then.
8 V BOOST FOR THE UV LED (LMR62014)
DISPLAY: 2.0 in ST7789 240x320 SPI TFT, 8-pin header

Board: 2 copper layers, 49 parts (0 on the bottom side), 36 nets, no tracks yet.

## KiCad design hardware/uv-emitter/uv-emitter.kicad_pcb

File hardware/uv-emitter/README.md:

# UV-Emitter

UV LED board: an Inolux IN-C35PPCTGU0 UV-C LED with its driver circuit.
Called **UV-LED-source** in the `uv-water` repository.

Open `uv-emitter.kicad_pro` in KiCad 10. Custom parts come from
[`lib/`](../../lib).

**[Download the KiCad files (zip)](https://github.com/edgecollective/uv254/archive/refs/heads/main.zip)**: the whole repository as it is on
`main`, because the board needs the shared `lib/` folder. This board is in
`hardware/uv-emitter/`.

<!-- render-images:start -->
<!-- Generated by scripts/render-images.sh. Edits between these markers are overwritten. -->

## Schematic

Click the image for the [PDF](docs/uv-emitter-schematic.pdf).

## Board layout

Copper and silkscreen. The back is mirrored, as seen from below.

| Front | Back |
|:---:|:---:|
|  |  |

## 3D view

| Front | Back |
|:---:|:---:|
|  |  |

Images of the current design, made with `scripts/render-images.sh uv-emitter`.
Re-run it after changing the board; see
[Updating the board images](../../README.md#updating-the-board-images).
<!-- render-images:end -->

## Revisions

| Version | Date | Status | Design | Fab files |
|---|---|---|---|---|
| v0.1 | 2024-03-11 | gerbers released | tag `uv-emitter/v0.1` | [`fab/v0.1`](fab/v0.1) |
| v0.2 | 2024-04-06 | gerbers released | tag `uv-emitter/v0.2` | [`fab/v0.2`](fab/v0.2) |
| v0.3 | 2024-08-19 | ordered from JLCPCB with detector v0.3 and control v0.1 | tag `uv-emitter/v0.3` | [`fab/v0.3`](fab/v0.3) |
| v0.2_A | 2026-06 to 2026-10 | design revision branched from v0.2, not fabricated | tag `uv-emitter/v0.2_A` | — |
| **v0.4** | 2026-11-08 | **gerbers released**; derived from v0.2_A | tag `uv-emitter/v0.4` | [`fab/v0.4`](fab/v0.4) |

Notes:

- **v0.3** has no `.kicad_pro`, because it was never committed upstream. Open
  `uv-emitter.kicad_pcb` or `.kicad_sch` directly at that tag.
- **v0.4** was called "v0.3" in `uv-water`. It was renumbered because v0.3 was
  already used by the 2024 JLCPCB order.

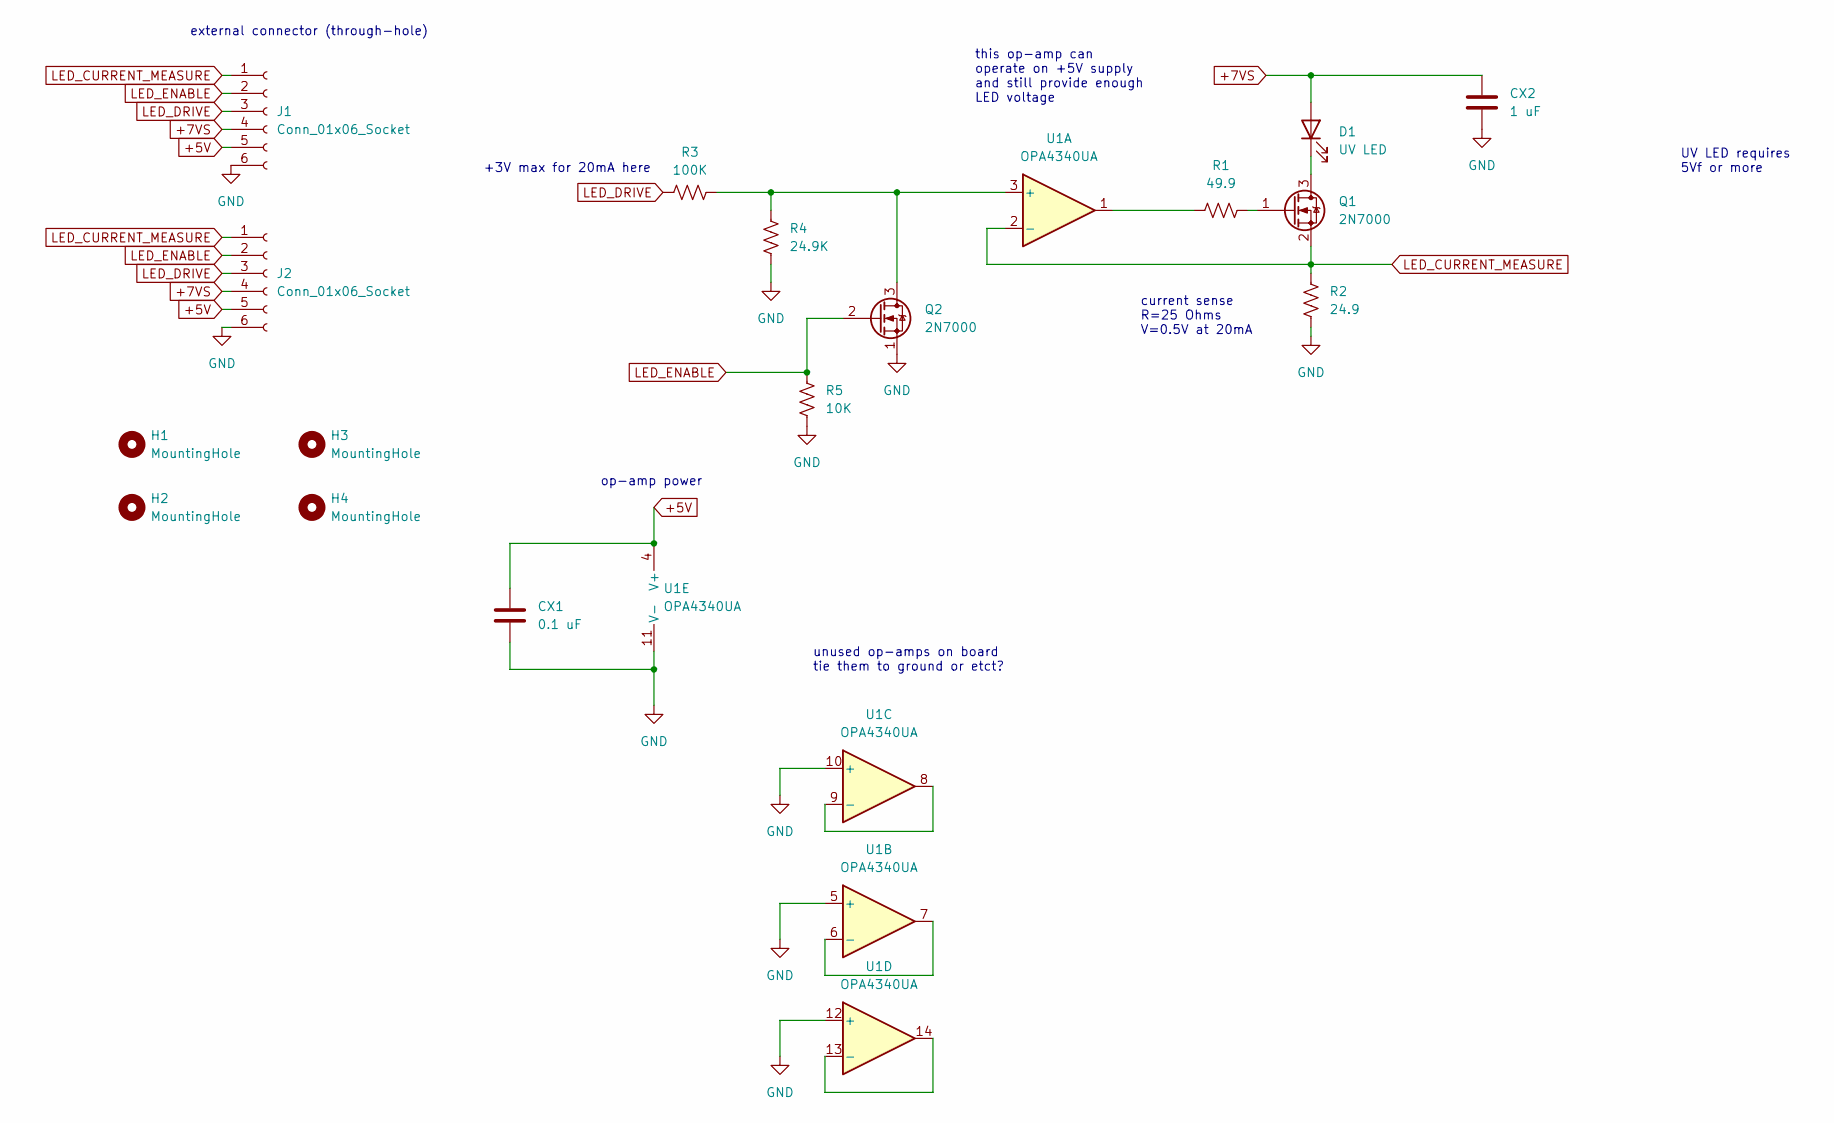
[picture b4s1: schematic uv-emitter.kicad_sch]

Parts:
CX1: 0.1 uF; C_0805_2012Metric_Pad1.18x1.45mm_HandSolder
CX2: 1 uF; C_0805_2012Metric_Pad1.18x1.45mm_HandSolder
D1: UV LED; LED_IN-C35PPCTGU0
H1, H2, H3, H4: MountingHole; MountingHole_3.2mm_M3
J1: Conn_01x06_Socket; PinSocket_1x06_P2.54mm_Vertical
J2: Conn_01x06_Socket; JST_PH_B6B-PH-K_1x06_P2.00mm_Vertical
Q1, Q2: 2N7000; SOT-23
R1: 49.9; R_0805_2012Metric_Pad1.20x1.40mm_HandSolder
R2: 24.9; R_0805_2012Metric_Pad1.20x1.40mm_HandSolder
R3: 100K; R_0805_2012Metric_Pad1.20x1.40mm_HandSolder
R4: 24.9K; R_0805_2012Metric_Pad1.20x1.40mm_HandSolder
R5: 10K; R_0805_2012Metric_Pad1.20x1.40mm_HandSolder
U1: OPA4340UA; SOIC-14_3.9x8.7mm_P1.27mm

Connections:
+5V: CX1.1, J1.5, J2.5, U1.4 (V+)
+7VS: CX2.1, D1.2 (A), J1.4, J2.4
GND: CX1.2, CX2.2, J1.6, J2.6, Q2.1 (S), R2.1, R4.1, R5.1, U1.5 (+), U1.10 (+), U1.11 (V-), U1.12 (+)
LED_CURRENT_MEASURE: J1.1, J2.1, Q1.2 (S), R2.2, U1.2 (-)
LED_DRIVE: J1.3, J2.3, R3.1
LED_ENABLE: J1.2, J2.2, Q2.2 (G), R5.2
unnamed: D1.1 (K), Q1.3 (D)
unnamed: Q1.1 (G), R1.2
unnamed: Q2.3 (D), R3.2, R4.2, U1.3 (+)
unnamed: R1.1, U1.1
unnamed: U1.6 (-), U1.7
unnamed: U1.8, U1.9 (-)
unnamed: U1.13 (-), U1.14

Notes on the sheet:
+3V max for 20mA here
UV LED requires 5Vf or more
external connector (through-hole)
this op-amp can operate on +5V supply and still provide enough LED voltage
current sense R=25 Ohms V=0.5V at 20mA
unused op-amps on board tie them to ground or etct?
op-amp power
